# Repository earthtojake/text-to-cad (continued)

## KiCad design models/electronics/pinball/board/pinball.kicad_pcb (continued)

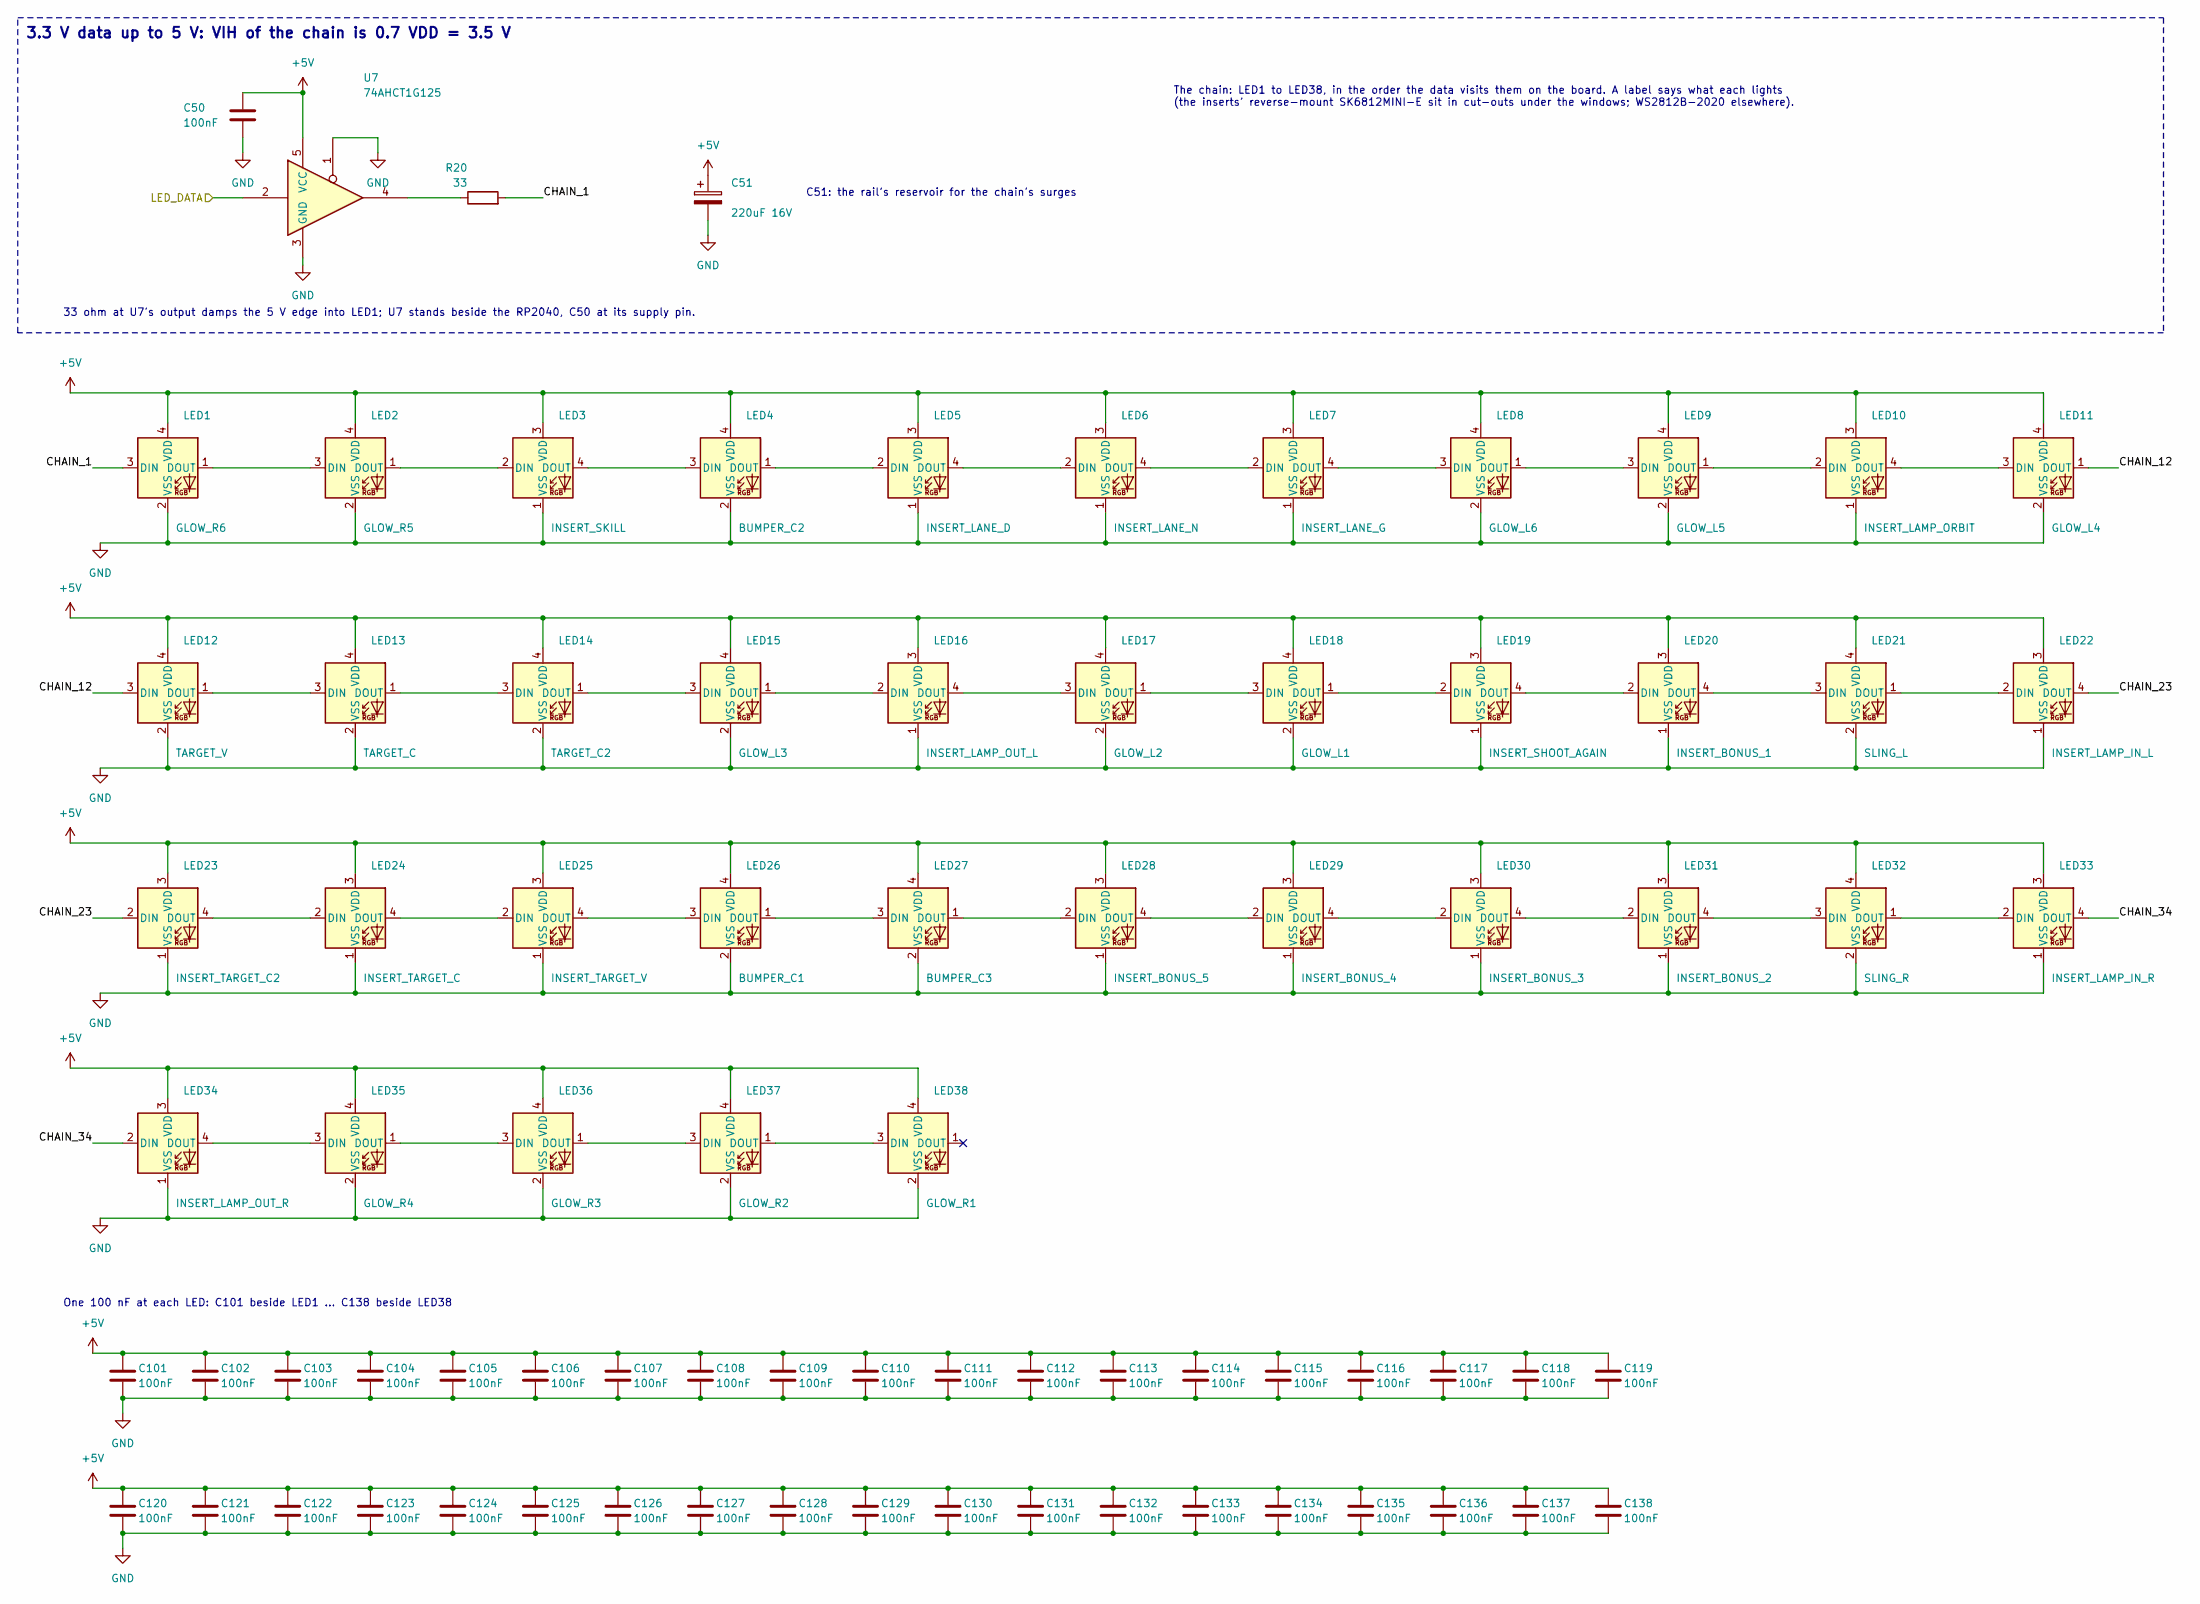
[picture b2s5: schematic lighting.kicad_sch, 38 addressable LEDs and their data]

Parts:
C50, C101, C102, C103, C104, C105, C106, C107, C108, C109, C110, C111, C112, C113, C114, C115, C116, C117, C118, C119, C120, C121, C122, C123, C124, C125, C126, C127, C128, C129, C130, C131, C132, C133, C134, C135, C136, C137, C138: 100nF; C_0402_1005Metric; MPN CL05B104KO5NNNC; LCSC C1525
C51: 220uF 16V; CP_Elec_8x10; MPN EEE-FK1C221P
LED1: GLOW_R6; LED_WS2812B-2020_PLCC4_2.0x2.0mm; MPN WS2812B-2020; LCSC C965555
LED2: GLOW_R5; LED_WS2812B-2020_PLCC4_2.0x2.0mm; MPN WS2812B-2020; LCSC C965555
LED3: INSERT_SKILL; LED_SK6812MINI-E_3.2x2.8mm_P1.5mm_ReverseMount; MPN SK6812MINI-E; LCSC C5149201
LED4: BUMPER_C2; LED_WS2812B-2020_PLCC4_2.0x2.0mm; MPN WS2812B-2020; LCSC C965555
LED5: INSERT_LANE_D; LED_SK6812MINI-E_3.2x2.8mm_P1.5mm_ReverseMount; MPN SK6812MINI-E; LCSC C5149201
LED6: INSERT_LANE_N; LED_SK6812MINI-E_3.2x2.8mm_P1.5mm_ReverseMount; MPN SK6812MINI-E; LCSC C5149201
LED7: INSERT_LANE_G; LED_SK6812MINI-E_3.2x2.8mm_P1.5mm_ReverseMount; MPN SK6812MINI-E; LCSC C5149201
LED8: GLOW_L6; LED_WS2812B-2020_PLCC4_2.0x2.0mm; MPN WS2812B-2020; LCSC C965555
LED9: GLOW_L5; LED_WS2812B-2020_PLCC4_2.0x2.0mm; MPN WS2812B-2020; LCSC C965555
LED10: INSERT_LAMP_ORBIT; LED_SK6812MINI-E_3.2x2.8mm_P1.5mm_ReverseMount; MPN SK6812MINI-E; LCSC C5149201
LED11: GLOW_L4; LED_WS2812B-2020_PLCC4_2.0x2.0mm; MPN WS2812B-2020; LCSC C965555
LED12: TARGET_V; LED_WS2812B-2020_PLCC4_2.0x2.0mm; MPN WS2812B-2020; LCSC C965555
LED13: TARGET_C; LED_WS2812B-2020_PLCC4_2.0x2.0mm; MPN WS2812B-2020; LCSC C965555
LED14: TARGET_C2; LED_WS2812B-2020_PLCC4_2.0x2.0mm; MPN WS2812B-2020; LCSC C965555
LED15: GLOW_L3; LED_WS2812B-2020_PLCC4_2.0x2.0mm; MPN WS2812B-2020; LCSC C965555
LED16: INSERT_LAMP_OUT_L; LED_SK6812MINI-E_3.2x2.8mm_P1.5mm_ReverseMount; MPN SK6812MINI-E; LCSC C5149201
LED17: GLOW_L2; LED_WS2812B-2020_PLCC4_2.0x2.0mm; MPN WS2812B-2020; LCSC C965555
LED18: GLOW_L1; LED_WS2812B-2020_PLCC4_2.0x2.0mm; MPN WS2812B-2020; LCSC C965555
LED19: INSERT_SHOOT_AGAIN; LED_SK6812MINI-E_3.2x2.8mm_P1.5mm_ReverseMount; MPN SK6812MINI-E; LCSC C5149201
LED20: INSERT_BONUS_1; LED_SK6812MINI-E_3.2x2.8mm_P1.5mm_ReverseMount; MPN SK6812MINI-E; LCSC C5149201
LED21: SLING_L; LED_WS2812B-2020_PLCC4_2.0x2.0mm; MPN WS2812B-2020; LCSC C965555
LED22: INSERT_LAMP_IN_L; LED_SK6812MINI-E_3.2x2.8mm_P1.5mm_ReverseMount; MPN SK6812MINI-E; LCSC C5149201
LED23: INSERT_TARGET_C2; LED_SK6812MINI-E_3.2x2.8mm_P1.5mm_ReverseMount; MPN SK6812MINI-E; LCSC C5149201
LED24: INSERT_TARGET_C; LED_SK6812MINI-E_3.2x2.8mm_P1.5mm_ReverseMount; MPN SK6812MINI-E; LCSC C5149201
LED25: INSERT_TARGET_V; LED_SK6812MINI-E_3.2x2.8mm_P1.5mm_ReverseMount; MPN SK6812MINI-E; LCSC C5149201
LED26: BUMPER_C1; LED_WS2812B-2020_PLCC4_2.0x2.0mm; MPN WS2812B-2020; LCSC C965555
LED27: BUMPER_C3; LED_WS2812B-2020_PLCC4_2.0x2.0mm; MPN WS2812B-2020; LCSC C965555
LED28: INSERT_BONUS_5; LED_SK6812MINI-E_3.2x2.8mm_P1.5mm_ReverseMount; MPN SK6812MINI-E; LCSC C5149201
LED29: INSERT_BONUS_4; LED_SK6812MINI-E_3.2x2.8mm_P1.5mm_ReverseMount; MPN SK6812MINI-E; LCSC C5149201
LED30: INSERT_BONUS_3; LED_SK6812MINI-E_3.2x2.8mm_P1.5mm_ReverseMount; MPN SK6812MINI-E; LCSC C5149201
LED31: INSERT_BONUS_2; LED_SK6812MINI-E_3.2x2.8mm_P1.5mm_ReverseMount; MPN SK6812MINI-E; LCSC C5149201
LED32: SLING_R; LED_WS2812B-2020_PLCC4_2.0x2.0mm; MPN WS2812B-2020; LCSC C965555
LED33: INSERT_LAMP_IN_R; LED_SK6812MINI-E_3.2x2.8mm_P1.5mm_ReverseMount; MPN SK6812MINI-E; LCSC C5149201
LED34: INSERT_LAMP_OUT_R; LED_SK6812MINI-E_3.2x2.8mm_P1.5mm_ReverseMount; MPN SK6812MINI-E; LCSC C5149201
LED35: GLOW_R4; LED_WS2812B-2020_PLCC4_2.0x2.0mm; MPN WS2812B-2020; LCSC C965555
LED36: GLOW_R3; LED_WS2812B-2020_PLCC4_2.0x2.0mm; MPN WS2812B-2020; LCSC C965555
LED37: GLOW_R2; LED_WS2812B-2020_PLCC4_2.0x2.0mm; MPN WS2812B-2020; LCSC C965555
LED38: GLOW_R1; LED_WS2812B-2020_PLCC4_2.0x2.0mm; MPN WS2812B-2020; LCSC C965555
R20: 33; R_0402_1005Metric; MPN 0402WGF330JTCE; LCSC C25105
U7: 74AHCT1G125; SOT-23-5; MPN SN74AHCT1G125DBVR; LCSC C7484

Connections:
+5V: C50.1, C51.1, C101.1, C102.1, C103.1, C104.1, C105.1, C106.1, C107.1, C108.1, C109.1, C110.1, C111.1, C112.1, C113.1, C114.1, C115.1, C116.1, C117.1, C118.1, C119.1, C120.1, C121.1, C122.1, C123.1, C124.1, C125.1, C126.1, C127.1, C128.1, C129.1, C130.1, C131.1, C132.1, C133.1, C134.1, C135.1, C136.1, C137.1, C138.1, LED1.4 (VDD), LED2.4 (VDD), LED3.3 (VDD), LED4.4 (VDD), LED5.3 (VDD), LED6.3 (VDD), LED7.3 (VDD), LED8.4 (VDD), LED9.4 (VDD), LED10.3 (VDD), LED11.4 (VDD), LED12.4 (VDD), LED13.4 (VDD), LED14.4 (VDD), LED15.4 (VDD), LED16.3 (VDD), LED17.4 (VDD), LED18.4 (VDD), LED19.3 (VDD), LED20.3 (VDD), LED21.4 (VDD), LED22.3 (VDD), LED23.3 (VDD), LED24.3 (VDD), LED25.3 (VDD), LED26.4 (VDD), LED27.4 (VDD), LED28.3 (VDD), LED29.3 (VDD), LED30.3 (VDD), LED31.3 (VDD), LED32.4 (VDD), LED33.3 (VDD), LED34.3 (VDD), LED35.4 (VDD), LED36.4 (VDD), LED37.4 (VDD), LED38.4 (VDD), U7.5 (VCC); also elsewhere on the board
/Lighting/CHAIN_1: LED1.3 (DIN), R20.2
/Lighting/CHAIN_12: LED11.1 (DOUT), LED12.3 (DIN)
/Lighting/CHAIN_23: LED22.4 (DOUT), LED23.2 (DIN)
/Lighting/CHAIN_34: LED33.4 (DOUT), LED34.2 (DIN)
/Lighting/LED_DATA: U7.2; also elsewhere on the board
GND: C50.2, C51.2, C101.2, C102.2, C103.2, C104.2, C105.2, C106.2, C107.2, C108.2, C109.2, C110.2, C111.2, C112.2, C113.2, C114.2, C115.2, C116.2, C117.2, C118.2, C119.2, C120.2, C121.2, C122.2, C123.2, C124.2, C125.2, C126.2, C127.2, C128.2, C129.2, C130.2, C131.2, C132.2, C133.2, C134.2, C135.2, C136.2, C137.2, C138.2, LED1.2 (VSS), LED2.2 (VSS), LED3.1 (VSS), LED4.2 (VSS), LED5.1 (VSS), LED6.1 (VSS), LED7.1 (VSS), LED8.2 (VSS), LED9.2 (VSS), LED10.1 (VSS), LED11.2 (VSS), LED12.2 (VSS), LED13.2 (VSS), LED14.2 (VSS), LED15.2 (VSS), LED16.1 (VSS), LED17.2 (VSS), LED18.2 (VSS), LED19.1 (VSS), LED20.1 (VSS), LED21.2 (VSS), LED22.1 (VSS), LED23.1 (VSS), LED24.1 (VSS), LED25.1 (VSS), LED26.2 (VSS), LED27.2 (VSS), LED28.1 (VSS), LED29.1 (VSS), LED30.1 (VSS), LED31.1 (VSS), LED32.2 (VSS), LED33.1 (VSS), LED34.1 (VSS), LED35.2 (VSS), LED36.2 (VSS), LED37.2 (VSS), LED38.2 (VSS), U7.1, U7.3 (GND); also elsewhere on the board
unnamed: LED1.1 (DOUT), LED2.3 (DIN)
unnamed: LED2.1 (DOUT), LED3.2 (DIN)
unnamed: LED3.4 (DOUT), LED4.3 (DIN)
unnamed: LED4.1 (DOUT), LED5.2 (DIN)
unnamed: LED5.4 (DOUT), LED6.2 (DIN)
unnamed: LED6.4 (DOUT), LED7.2 (DIN)
unnamed: LED7.4 (DOUT), LED8.3 (DIN)
unnamed: LED8.1 (DOUT), LED9.3 (DIN)
unnamed: LED9.1 (DOUT), LED10.2 (DIN)
unnamed: LED10.4 (DOUT), LED11.3 (DIN)
unnamed: LED12.1 (DOUT), LED13.3 (DIN)
unnamed: LED13.1 (DOUT), LED14.3 (DIN)
unnamed: LED14.1 (DOUT), LED15.3 (DIN)
unnamed: LED15.1 (DOUT), LED16.2 (DIN)
unnamed: LED16.4 (DOUT), LED17.3 (DIN)
unnamed: LED17.1 (DOUT), LED18.3 (DIN)
unnamed: LED18.1 (DOUT), LED19.2 (DIN)
unnamed: LED19.4 (DOUT), LED20.2 (DIN)
unnamed: LED20.4 (DOUT), LED21.3 (DIN)
unnamed: LED21.1 (DOUT), LED22.2 (DIN)
unnamed: LED23.4 (DOUT), LED24.2 (DIN)
unnamed: LED24.4 (DOUT), LED25.2 (DIN)
unnamed: LED25.4 (DOUT), LED26.3 (DIN)
unnamed: LED26.1 (DOUT), LED27.3 (DIN)
unnamed: LED27.1 (DOUT), LED28.2 (DIN)
unnamed: LED28.4 (DOUT), LED29.2 (DIN)
unnamed: LED29.4 (DOUT), LED30.2 (DIN)
unnamed: LED30.4 (DOUT), LED31.2 (DIN)
unnamed: LED31.4 (DOUT), LED32.3 (DIN)
unnamed: LED32.1 (DOUT), LED33.2 (DIN)
unnamed: LED34.4 (DOUT), LED35.3 (DIN)
unnamed: LED35.1 (DOUT), LED36.3 (DIN)
unnamed: LED36.1 (DOUT), LED37.3 (DIN)
unnamed: LED37.1 (DOUT), LED38.3 (DIN)
unnamed: R20.1, U7.4

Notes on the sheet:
3.3 V data up to 5 V: VIH of the chain is 0.7 VDD = 3.5 V
33 ohm at U7's output damps the 5 V edge into LED1; U7 stands beside the RP2040, C50 at its supply pin.
C51: the rail's reservoir for the chain's surges
The chain: LED1 to LED38, in the order the data visits them on the board. A label says what each lights (the inserts' reverse-mount SK6812MINI-E sit in cut-outs under the windows; WS2812B-2020 elsewhere).
One 100 nF at each LED: C101 beside LED1 ... C138 beside LED38

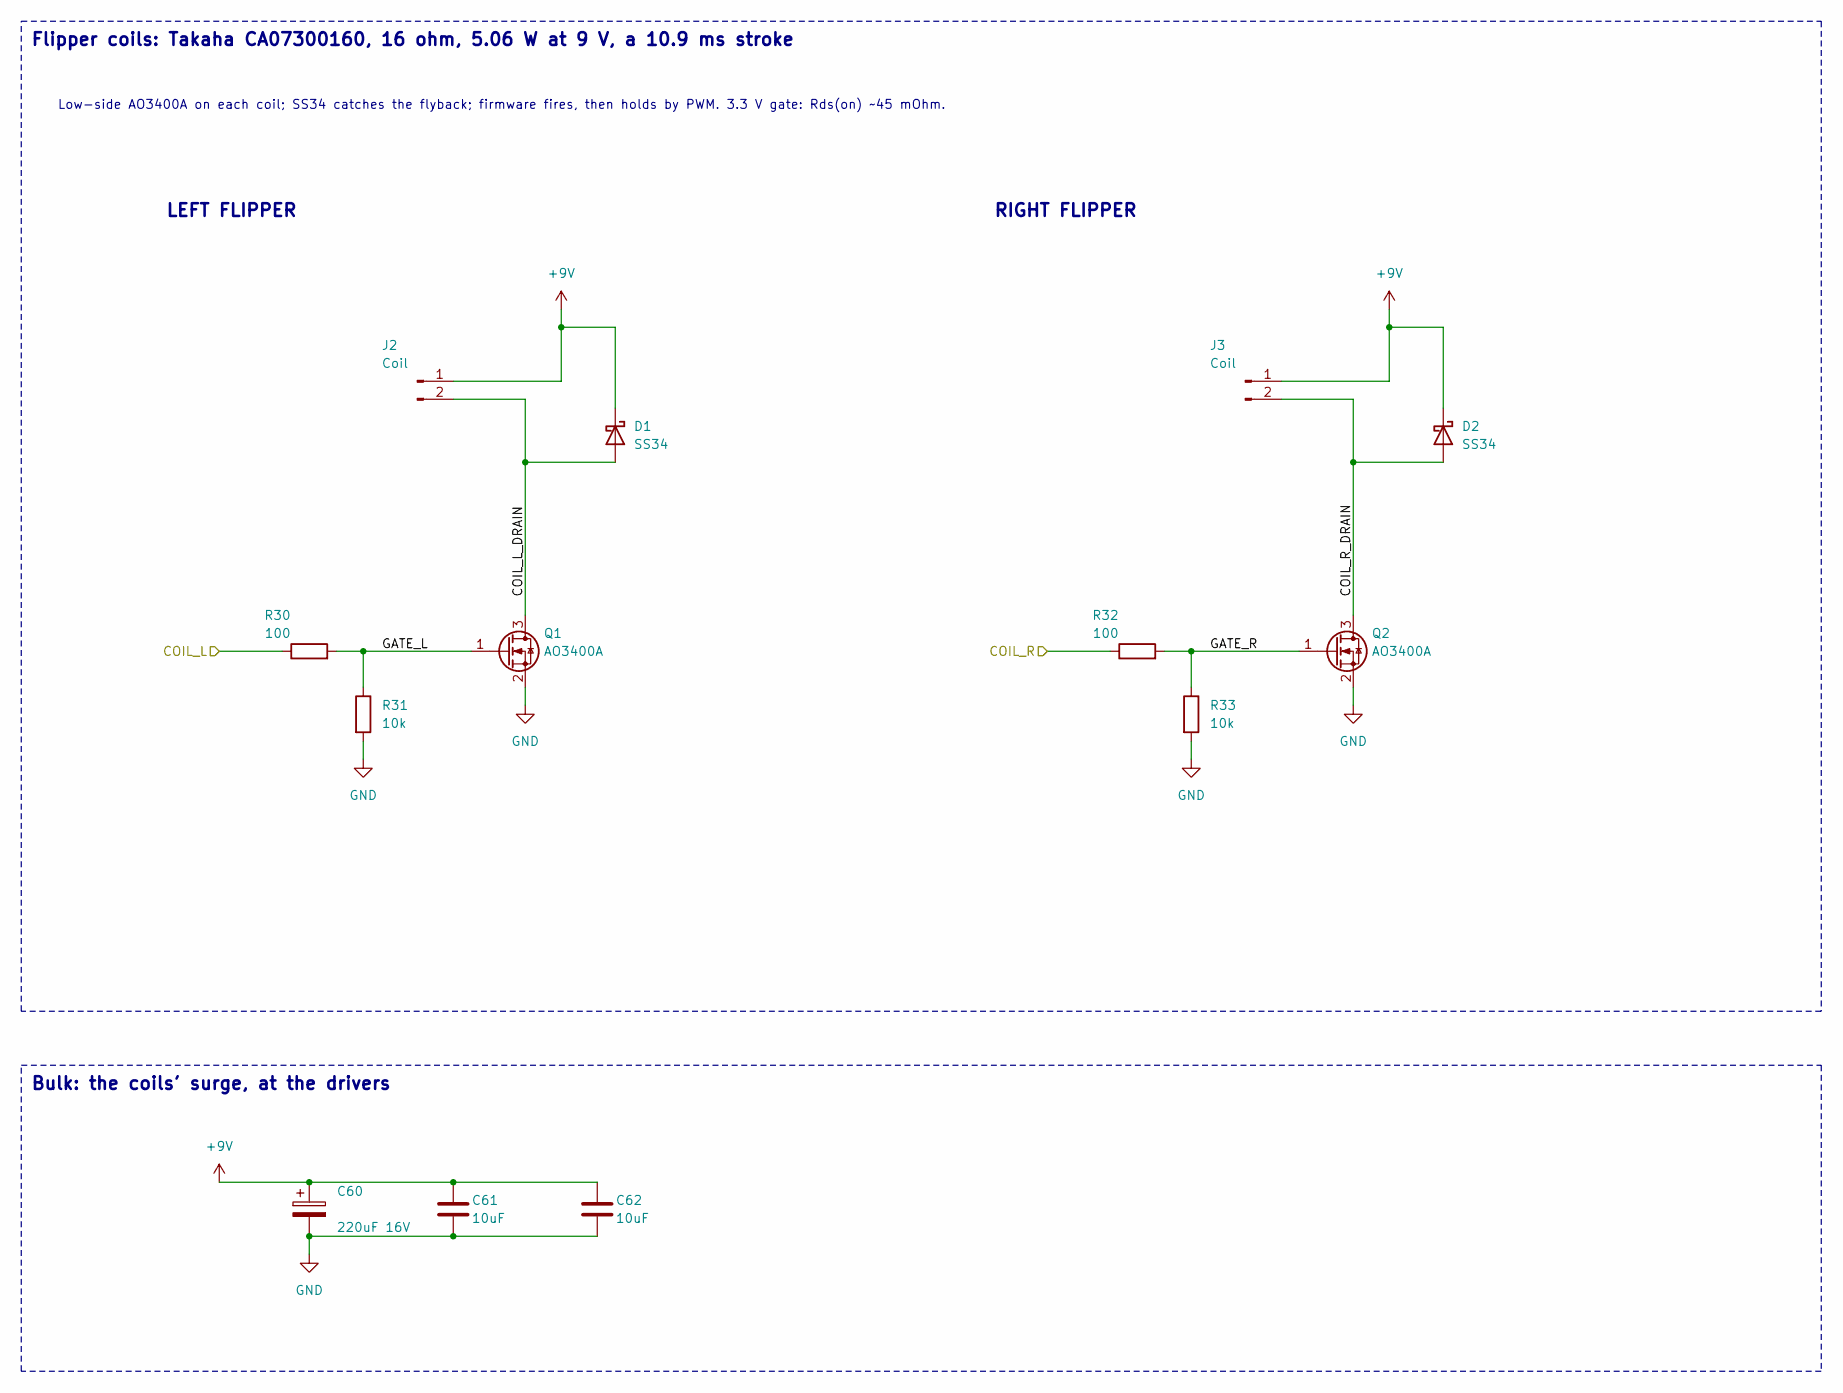
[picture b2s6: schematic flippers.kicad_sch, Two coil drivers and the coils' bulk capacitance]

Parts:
C60: 220uF 16V; CP_Elec_8x10; MPN EEE-FK1C221P
C61, C62: 10uF; C_0805_2012Metric; MPN CL21A106KAYNNNE; LCSC C15850
D1, D2: SS34; D_SMA; MPN SS34; LCSC C8678
J2, J3: Coil; JST_PH_B2B-PH-K_1x02_P2.00mm_Vertical; MPN B2B-PH-K-S; LCSC C131337
Q1, Q2: AO3400A; SOT-23; MPN AO3400A; LCSC C20917
R30, R32: 100; R_0402_1005Metric; MPN 0402WGF1000TCE; LCSC C25076
R31, R33: 10k; R_0402_1005Metric; MPN 0402WGF1002TCE; LCSC C25744

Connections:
+9V: C60.1, C61.1, C62.1, D1.1 (K), D2.1 (K), J2.1, J3.1; also elsewhere on the board
/Flippers/COIL_L: R30.1; also elsewhere on the board
/Flippers/COIL_L_DRAIN: D1.2 (A), J2.2, Q1.3 (D)
/Flippers/COIL_R: R32.1; also elsewhere on the board
/Flippers/COIL_R_DRAIN: D2.2 (A), J3.2, Q2.3 (D)
/Flippers/GATE_L: Q1.1 (G), R30.2, R31.1
/Flippers/GATE_R: Q2.1 (G), R32.2, R33.1
GND: C60.2, C61.2, C62.2, Q1.2 (S), Q2.2 (S), R31.2, R33.2; also elsewhere on the board

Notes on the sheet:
Flipper coils: Takaha CA07300160, 16 ohm, 5.06 W at 9 V, a 10.9 ms stroke
Low-side AO3400A on each coil; SS34 catches the flyback; firmware fires, then holds by PWM. 3.3 V gate: Rds(on) ~45 mOhm.
LEFT FLIPPER
RIGHT FLIPPER
Bulk: the coils' surge, at the drivers

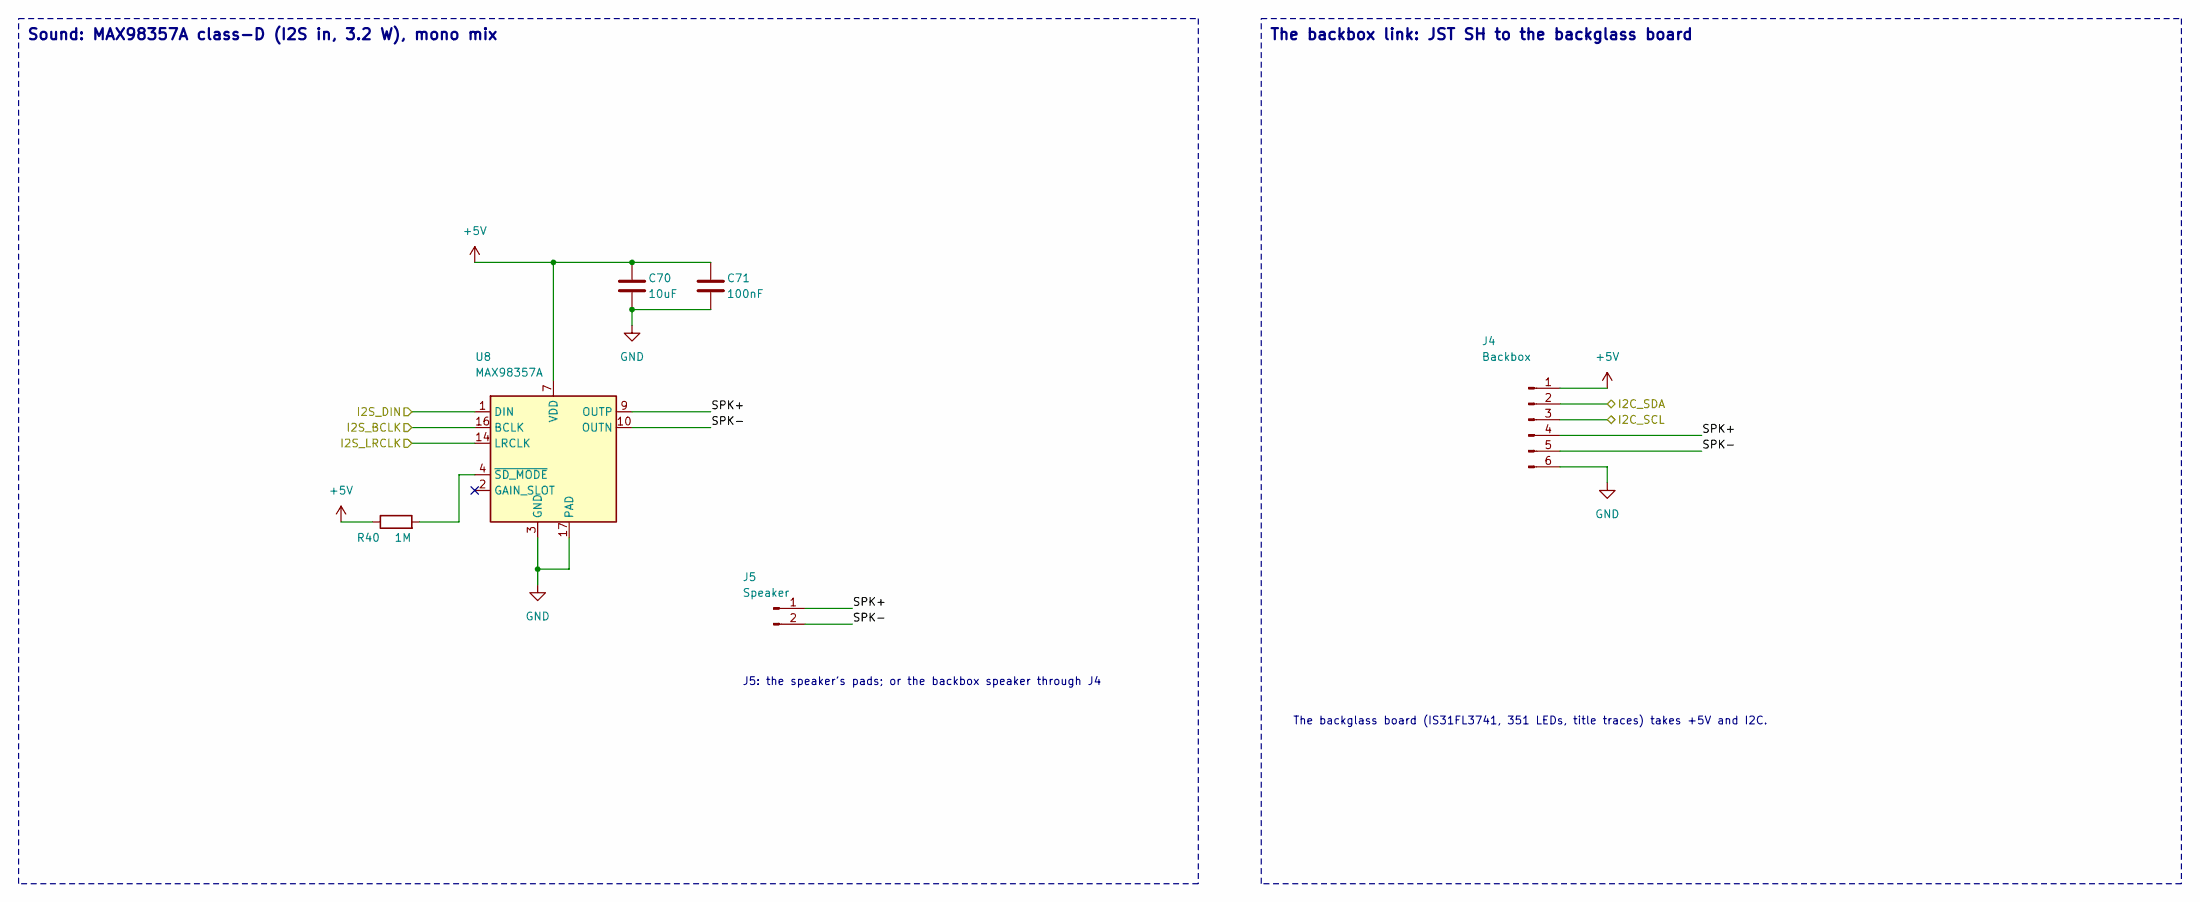
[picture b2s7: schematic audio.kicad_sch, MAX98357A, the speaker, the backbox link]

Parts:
C70: 10uF; C_0805_2012Metric; MPN CL21A106KAYNNNE; LCSC C15850
C71: 100nF; C_0402_1005Metric; MPN CL05B104KO5NNNC; LCSC C1525
J4: Backbox; JST_SH_SM06B-SRSS-TB_1x06-1MP_P1.00mm_Horizontal; MPN SM06B-SRSS-TB; LCSC C160404
J5: Speaker; SpeakerPads_2x3mm
R40: 1M; R_0402_1005Metric; MPN 0402WGF1004TCE; LCSC C26083
U8: MAX98357A; TQFN-16-1EP_3x3mm_P0.5mm_EP1.23x1.23mm; MPN MAX98357AETE+T; LCSC C910544

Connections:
+5V: C70.1, C71.1, J4.1, R40.1, U8.7 (VDD), U8.8 (VDD); also elsewhere on the board
/Audio and backbox/I2S_BCLK: U8.16 (BCLK); also elsewhere on the board
/Audio and backbox/I2S_DIN: U8.1 (DIN); also elsewhere on the board
/Audio and backbox/I2S_LRCLK: U8.14 (LRCLK); also elsewhere on the board
/Audio and backbox/SPK+: J4.4, J5.1, U8.9 (OUTP)
/Audio and backbox/SPK-: J4.5, J5.2, U8.10 (OUTN)
/I2C_SCL: J4.3; also elsewhere on the board
/I2C_SDA: J4.2; also elsewhere on the board
GND: C70.2, C71.2, J4.6, U8.3 (GND), U8.11 (GND), U8.15 (GND), U8.17 (PAD); also elsewhere on the board
unnamed: R40.2, U8.4 (~SD_MODE)

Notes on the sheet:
Sound: MAX98357A class-D (I2S in, 3.2 W), mono mix
J5: the speaker's pads; or the backbox speaker through J4
The backbox link: JST SH to the backglass board
The backglass board (IS31FL3741, 351 LEDs, title traces) takes +5V and I2C.

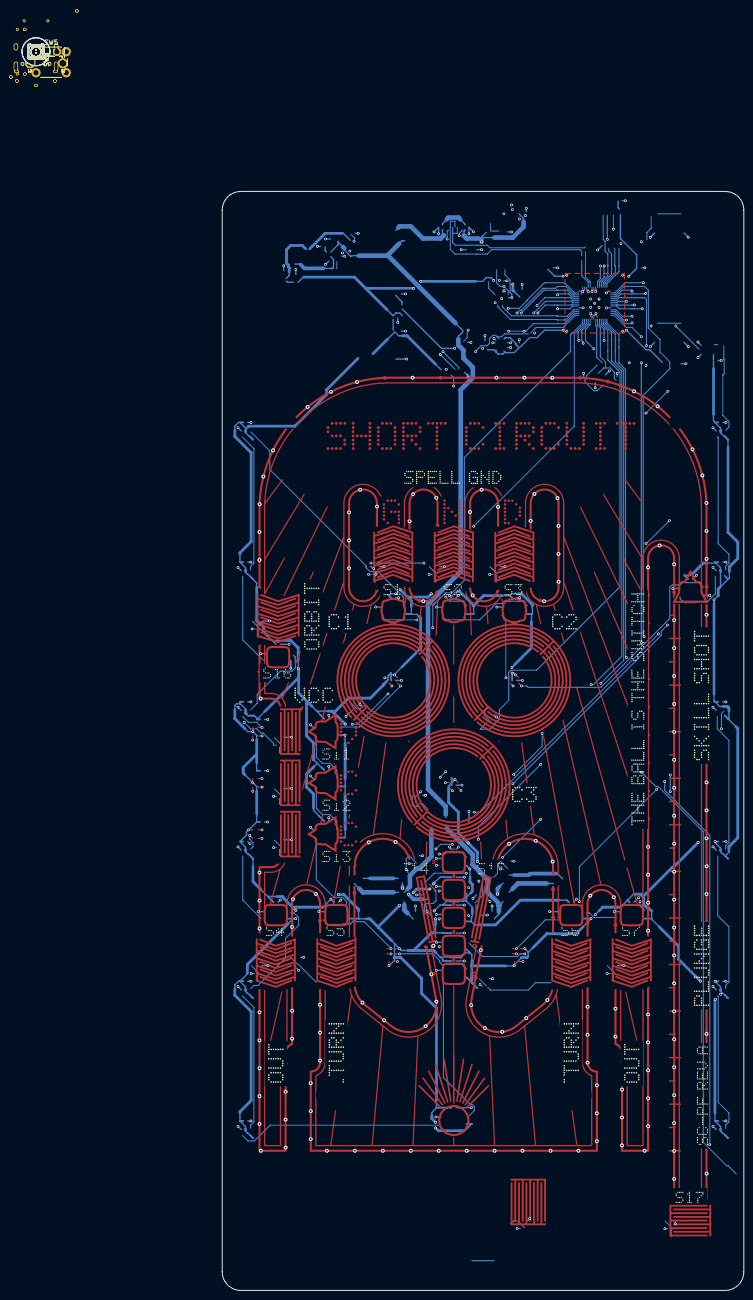
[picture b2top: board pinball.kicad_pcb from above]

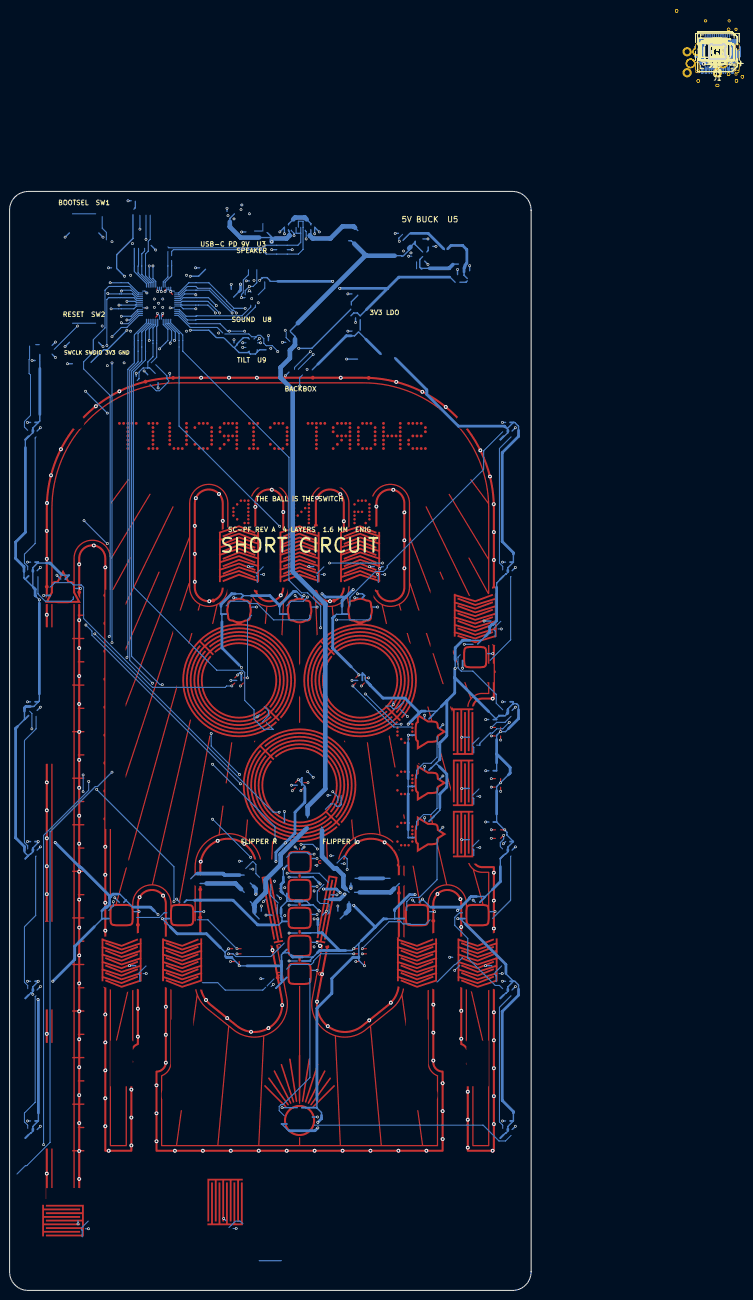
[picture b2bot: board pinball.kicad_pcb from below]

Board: 4 copper layers, 3.6 x 3.2 mm, 250 parts (173 on the bottom side), 125 nets.

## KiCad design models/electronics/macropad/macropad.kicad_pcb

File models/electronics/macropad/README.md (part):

# Nine: a 3x3 RP2040 macropad, board and case designed together

**Build the board first.** Its KiCad files (the board, the four schematic sheets, the project file and its rules,
the footprint library) are generated by `scripts/`, not committed: `cad run build.py`, from this folder, makes them
in about 20 s. It needs the `cad` command (KiCad 10.99's kicad-cli and API come with it) and KiCad's stock libraries
(macOS's KiCad.app, or `KICAD10_SYMBOL_DIR` and `KICAD10_FOOTPRINT_DIR`). Opening the board or the schematic in the
viewer or in KiCad, the checks and the case (`src/`) all read what it writes, so run it before any of them.

Nine is a nine-key mechanical macropad with a knob: an RP2040 with 16 MB of QSPI flash, USB-C, nine
hot-swap MX switches each with its own RGB LED shining through the switch, and an EC11 rotary
encoder with a push switch. Its 3D-printed case (a tray and an integrated switch plate) is generated
from the board file: the switch cut-outs, the screw bosses, the encoder window, the USB-C opening
and the BOOT/RESET pinholes are all read from `macropad.kicad_pcb`, so moving a part on the board
and running the case again moves the case's feature with it.

Why it is interesting to watch: a familiar, desirable object goes from a schematic to a routed,
DRC-clean two-layer board to a printable case and an exploding assembly, every step a prompt.

## The parts

| Ref | Part | Why |
| --- | --- | --- |
| U1 | RP2040 (QFN-56) | dual Cortex-M0+, native USB 1.1 full speed, 30 GPIO |
| U2 | W25Q128JVSIQ, 16 MB QSPI flash (SOIC-8) | the RP2040 boots from it |
| Y1 | 12 MHz crystal, ABM8-272-T3 (3225), 15 pF loads, 1 k on XOUT | RP2040's reference design values |
| U3 | AP2112K-3.3 LDO, 600 mA | 3.3 V from USB 5 V |
| J1 | GCT USB4105-GF-A, USB-C 2.0 receptacle | with 5.1 k Rd on CC1/CC2 (R1, R2): a USB-C sink |
| U4 | Nexperia PRTR5V0U2X | ESD clamps on D+/D- (shunt type, so the pair runs straight past it) |
| F1 | 500 mA polyfuse | VBUS to +5V |
| SW1-SW9 | Kailh CPG151101S11 MX hot-swap sockets | 19.05 mm pitch, plate-mount MX switches |
| D1-D9 | SK6812MINI-E reverse-mount RGB | under each switch's LED window, chained |
| U5 | 74AHCT1G125 | 3.3 V -> 5 V data for the LEDs (VIH 0.7 VDD = 3.5 V) |
| SW10 | Alps EC11E with switch, 20 mm shaft | the knob |
| SW11, SW12 | Omron B3U-1000P | BOOTSEL and RESET, pressed through the tray |
| TP1-TP4 | test pads | SWCLK, SWDIO, GND, 3V3 |
| H1-H6 | M2 holes | four between the keys, two in the back corners |

**Direct wiring, no matrix.** Nine keys, three encoder lines and the LED data use 13 of the RP2040's
30 GPIOs, so each key has its own pin (internal pull-up, switch to ground): no diodes (nine fewer
parts), every combination of keys reads without ghosting, and the firmware is a plain GPIO read. A
3x3 matrix would save 3 pins the board does not need.

**Every SMD part is on the bottom.** The hot-swap sockets and the reverse-mount LEDs have to be there
anyway, so the whole board assembles in one SMT pass; the top holds only the switches (in their
sockets) and the encoder. Two copper layers: the bottom carries the parts, the signals and power, the
top is a ground pour crossed only by the key lines in channels between the key columns (under the
switches' plastic) and a few short hops.

## The board

| | |
| --- | --- |
| Size | 59.0 x 83.5 mm, 1.6 mm FR-4, rounded corners r 3 mm |
| Layers | 2 (1 oz); both are ground pours |
| Parts | 73 footprints: 63 to assemble (all SMD on the bottom; the encoder is through-hole), 6 M2 holes, 4 test pads |
| Nets | 46 connected (KiCad adds 21 more, one on each unconnected pin) |
| Routing | 371 tracks, 1384 mm of copper, 81 vias; 0 unconnected |
| ERC | clean, 0 warnings (`cad kicad_sch erc macropad.kicad_sch`) |
| DRC | clean: 0 errors, 0 warnings (`cad kicad_pcb drc macropad.kicad_pcb` on the built board) |
| Rules | JLCPCB standard 2-layer, read 2026-11-04 from the pcb skill's table of jlcpcb.com/capabilities: 0.15 mm space (fab 0.10), 0.2 mm signal tracks, 0.3/0.6 mm vias, 0.3 mm copper to edge (0.2 at the LEDs' own cut-outs, the fab's limit) |

Hierarchical schematic: the root (`macropad.kicad_sch`) and three sheets, `usb_power` (USB-C, CC,
ESD, polyfuse, LDO), `mcu` (RP2040, flash, crystal, boot, reset, SWD, decoupling) and `keys`
(switches, encoder, level shifter, LEDs, holes). GPIO map: ENC_SW GP0, ENC_B GP1, ENC_A GP2,
KEY9/6/3 GP3/4/5, KEY8/5/2 GP9/10/11, KEY7/4/1 GP26/27/29, LED data GP28. The map was chosen from
the board: each group leaves the RP2040 on the side facing where it goes, in the order it arrives.

The RP2040's own ring (between its pads and its exposed pad) carries two rails, 1V1 from VREG_VOUT
to both DVDD pins and 3V3 to IOVDD 1, 10 and 22, which keeps the USB pair and the QSPI fan-out
uncrossed on a two-layer board.

KiCad's library has no MX hot-swap footprint and no 3D model for a keyboard switch or an EC11, so the
project carries its own: `macropad.pretty` holds the hot-swap socket's footprint (drawn from the Kailh
CPG151101S11 land pattern, mirrored for the bottom) and KiCad's EC11 footprint naming a model, and
`src/vendor_parts.py` draws both models. Check the socket's land pattern against a real socket before
ordering.

Review (guided, not a fab's CAM check): DRC clean against the rules above; every pad on its
schematic pin's net, all track segments at 45-degree steps, no track narrower than its current
(+5V/VBUS 0.5 mm for 0.6 A), each decoupler within 3 mm of its pin and ground under every point of
the USB pair (`check_macropad.py`); USB pair skew 0.6 mm (connector side) and 1.1 mm (MCU side),
immaterial at full speed's 83 ns bits. Items for a person: C13 (USB_VDD + IOVDD 49) sits 4.5 mm from
its pins (the spot beside them holds the USB pair and the QSPI fan-out); DVDD 50 has no cap of its own
(it is ringed to VREG_VOUT 45's 1 uF and DVDD 23's 100 nF); IOVDD 22's cap C9 is placed by pin 33;
the LED supply (0.54 A at full white) exceeds USB 2.0's 500 mA: firmware must cap brightness. The
stock SK6812MINI-E footprint's pads sit 0.247 mm from its own cut-out, so a custom rule allows 0.2 mm
(JLCPCB's limit) for the LEDs; its pin numbers differ from the OPSCO datasheet's, but symbol and
footprint agree and each pad sits where the mirrored top view puts its function. Not checked: Gerbers
in a Gerber viewer, impedance, the BOM's sourcing beyond the LCSC numbers given, the hot-swap land
pattern against a physical socket.

## The case

Printed in PLA or PETG on an FDM printer, all parts without supports:

- **Tray** (floor down): 2 mm floor 5.4 mm under the board, 2.4 mm walls 0.4 mm off the board's
  edge, six bosses (6 mm) with M2 x 3 mm heat-set insert holes (3.2 mm) under the board's holes, a
  13 mm USB-C slot at the receptacle, 2.5 mm pinholes under BOOT and RESET.
- **Plate** (top face down): 1.5 mm, its top 5.0 mm above the board (MX), a 14.1 mm cut-out at each
  key, the encoder body's window, 4.6 mm spacer bosses down to the board at each hole (M2 clearance
  2.4 mm), NINE stencilled beside the knob.
- **Keycaps** (top down, x9): one shape, legend-free, 18 mm base, 12.6 mm top, 7.6 mm tall, MX cross
  4.2 x 1.35 mm; `keycap_body(dish=...)` scoops the top (flat by default, so it prints face down).
- **Knob** (top down): 19 mm, 24 grip flutes, a D-bore for the EC11's 6 mm shaft, a pointer groove.

Hardware: six M2 x 10 mm button-head screws (through the plate, its spacer and the board into the
tray's inserts), six M2 x 3 mm heat-set inserts, four stick-on rubber feet, nine MX-style switches.

Everything the case is built around comes from `macropad.kicad_pcb` through
`src/lib/board_geometry.py`: the outline and its corner radius, the six holes, the nine switch
positions, the encoder's shaft and body (and its rotation, which turns the knob's D-bore), the USB
receptacle's x and mating face, the two buttons.

## Files

| Path | What |
| --- | --- |
| `build.py` | the one command that makes the KiCad project: every step of `scripts/` in order |
| `scripts/` | the source of the board: footprints, schematic, rules, netlist import, placement, routing, silkscreen |
| `fp-lib-table`, `sym-lib-table` | the project's library tables (KiCad's stock libraries through `${KICAD10_FOOTPRINT_DIR}` and `${KICAD10_SYMBOL_DIR}`), the only KiCad files kept: no script writes them |
| `check_macropad.py` | the board's own checks |
| `src/` | the case: `vendor_parts.py` (the socket, the EC11 and an MX switch), `case.py`, `assembly.py`, `check_fit.py`, `exports.py`, `lib/board_geometry.py` |

Nothing generated is committed: the KiCad project `build.py` writes (`macropad.kicad_pro`, `.kicad_pcb`,
`.kicad_dru`, `macropad.kicad_sch` and its `usb_power`, `mcu` and `keys` sheets, `macropad.pretty/`, all in KiCad
10.99's format), the footprints' 3D models (`macropad.3dshapes/`), the fabrication files (`fab/`), the board's STEP
and the case's files (`STEP/`, `XBF/`, `GLB/`, `3MF/`, `DXF/`) are written by the commands below, and `.gitignore`
keeps them out of Git.

## Rebuild

From this folder, with the `cad` command. KiCad's stock libraries are named through
`${KICAD10_SYMBOL_DIR}` and `${KICAD10_FOOTPRINT_DIR}`, which ERC and DRC read in the KiCad you installed:
nothing to set. The generators (`gen_footprints.py`, `gen_schematic.py`) read the same libraries in macOS's
KiCad.app; elsewhere, give them KiCad's folders in those two variables.

```bash
# the board and its schematic, from scripts/ (each step states the board it wants; rerunning is harmless)
cad run build.py                           # about 20 s: the steps below, in order
#   scripts/gen_footprints.py              macropad.pretty
#   scripts/gen_schematic.py               the four sheets
#   scripts/step1_import.py                the board (KiCad makes it, with its project) and the netlist
#   scripts/step0_rules.py                 JLCPCB rules and netclasses into the project, the custom rules
#   scripts/step2_place.py                 outline, every part's place, side and angle
#   scripts/route.py                       every track and via, then the pours
#   scripts/step4_silk.py                  silkscreen

# the 3D models KiCad's library lacks: run this before opening the board in 3D or exporting its STEP or GLB
cad run src/vendor_parts.py                # macropad.3dshapes/: the hot-swap socket and the EC11

# check the board
cad kicad_sch erc macropad.kicad_sch
cad kicad_pcb drc macropad.kicad_pcb
cad run check_macropad.py                  # prints nothing when the board is clean

# fabrication files
for k in gerbers drill pos bom pdf; do cad kicad_pcb export macropad.kicad_pcb --to $k -o fab/$k; done
cad kicad_sch export macropad.kicad_sch --to pdf -o fab/schematic
cad kicad_pcb export macropad.kicad_pcb --to dxf -o DXF     # the outline and drilled holes
cad kicad_pcb export macropad.kicad_pcb --to glb -o GLB     # the board with its parts, to look at

# the case, read from the board: its STEP with every part, converted once to an xbf
cad kicad_pcb export macropad.kicad_pcb --to step -o STEP   # STEP/macropad.step
cad step export STEP/macropad.step XBF/macropad.xbf
cad run src/case.py                        # tray, plate, keycap, knob and their print orientations
cad run src/assembly.py                    # nine (with its explode) and nine_exploded
cad run src/check_fit.py                   # overlap volumes and clearances against the board's STEP
cad run src/exports.py                     # 3MF/ and STEP/ of each printed part, STEP/nine.step, GLB/nine.glb
cad threemf dfm 3MF/tray.3mf --process printing --angle-limit 45 --samples 20000   # and plate, keycap, knob
```

`gen_footprints.py`, `gen_schematic.py` and `step0_rules.py` write the same files on every run; the layout steps
make the same board, its items under new ids.

## The case's checks

**Fit** (`src/check_fit.py`, against KiCad's STEP of the board with every part): 297 pairs of solids
whose boxes meet, overlap volume 0 for all (tray, plate, switches, keycaps and knob each against
every board solid; switches, keycaps and knob against the plate; tray against plate). The board
rests on the tray's bosses (distance 0) with 0.4 mm to the tray's walls; the tray's floor is
2.0 mm under the lowest bottom part (the USB-C receptacle, z -3.4); the plate's underside is
3.59 mm above the bare board (MX: 3.5 plus the copper); each keycap is 1.2 mm clear of its switch;
the knob's D-bore sits on the EC11's shaft with the bore turned to the encoder's rotation.

**Printing** (`cad threemf dfm 3MF/<part>.3mf --process printing --angle-limit 45 --samples 20000`; FDM limits
from the cad skill's printing reference: 1.2 mm supported wall, 45 degrees, 10 mm bridge):

| Part | Overhangs under 45 deg | Walls min / p05 | Support | Result |
| --- | --- | --- | --- | --- |
| tray (floor down) | 0 mm2 | 1.38 / 2.0 mm | 0 | pass |
| plate (top down) | 0 mm2 | 0.04 / 1.5 mm | 0 | review: the thin readings are the acute inside corner of the stencil N, a wedge down to its tip; the plate is 1.5 mm |
| keycap (top down) | 0 mm2 | 0.53 / 1.2 mm | 0 | review: the MX cross (4.2 x 1.35 mm) inside the 5.5 mm stem leaves 0.53 mm at the cross's ends; the stem cannot grow (it travels into the switch's 5.6 mm opening). Print with a 0.25 mm nozzle, or in resin |
| knob (top down) | 3 mm2 (the 1 mm pointer groove, on the bed face) | 0.25 / 5.08 mm | 3 mm3 | review: the pointer groove ends 0.25 mm from the flute beyond it, for the groove's 1 mm depth |

What the check found and what changed: the tray's foot recesses (220 mm2 of 0.8 mm ceilings and
1.0 mm floors) are gone (stick-on feet instead) and the screw pilots stop 1.4 mm above the bed; the
plate's corner spacers at H5/H6 thinned to 0.55 mm against the tray's corner and are gone (the wall
carries the plate there); the engraved NINE (43 mm2 of ceilings face down) is now a through stencil;
the knob's flutes run full height (no ceilings), and its pointer groove, first modelled 0.1 mm under
the top face (a sealed void under a 0.1 mm skin), is open on the top. Not measured by the check:
minimum hole (the paperclip holes are 2.5 mm, the screw holes 2.4 mm, both over FDM's 2.0), bridges
(none), fit of the heat-set inserts (3.2 mm holes for M2 x 3 inserts, the insert maker's figure).

## Demo video script (about 3 minutes)

Record the CAD app (or the viewer) beside the agent's chat. Every prompt is what the person types;
the agent runs the skills. Pre-build everything once the day before so each shot replays warm.

| # | Prompt (typed to the agent) | What the viewer shows | Length | The one thing |
| --- | --- | --- | --- | --- |
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
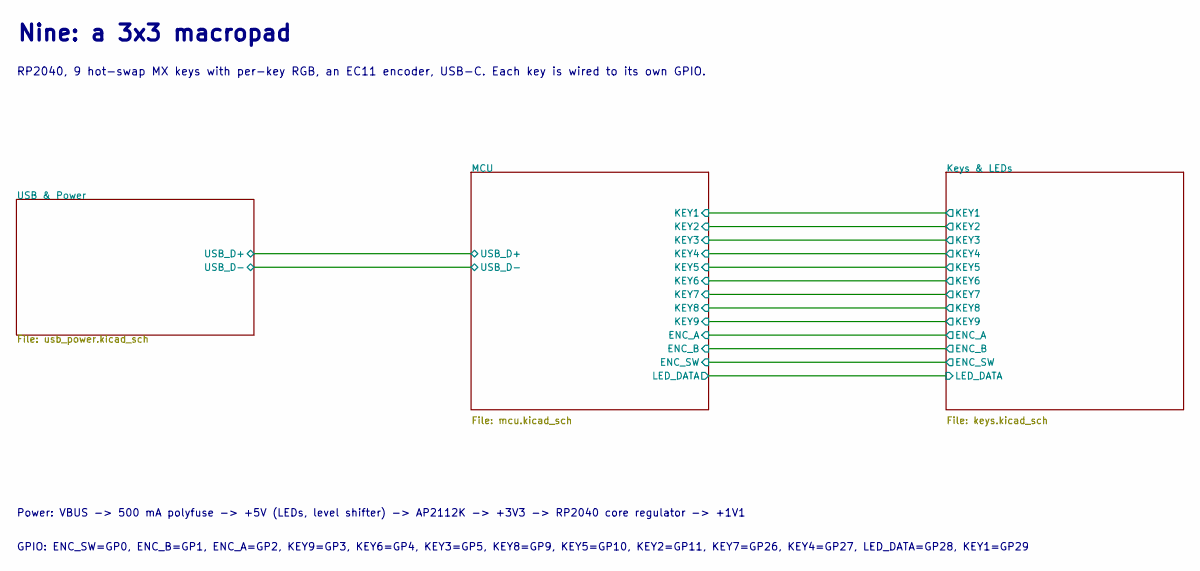
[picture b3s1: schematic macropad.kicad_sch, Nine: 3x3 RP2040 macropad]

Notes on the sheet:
Nine: a 3x3 macropad
RP2040, 9 hot-swap MX keys with per-key RGB, an EC11 encoder, USB-C. Each key is wired to its own GPIO.
Power: VBUS -> 500 mA polyfuse -> +5V (LEDs, level shifter) -> AP2112K -> +3V3 -> RP2040 core regulator -> +1V1
GPIO: ENC_SW=GP0, ENC_B=GP1, ENC_A=GP2, KEY9=GP3, KEY6=GP4, KEY3=GP5, KEY8=GP9, KEY5=GP10, KEY2=GP11, KEY7=GP26, KEY4=GP27, LED_DATA=GP28, KEY1=GP29

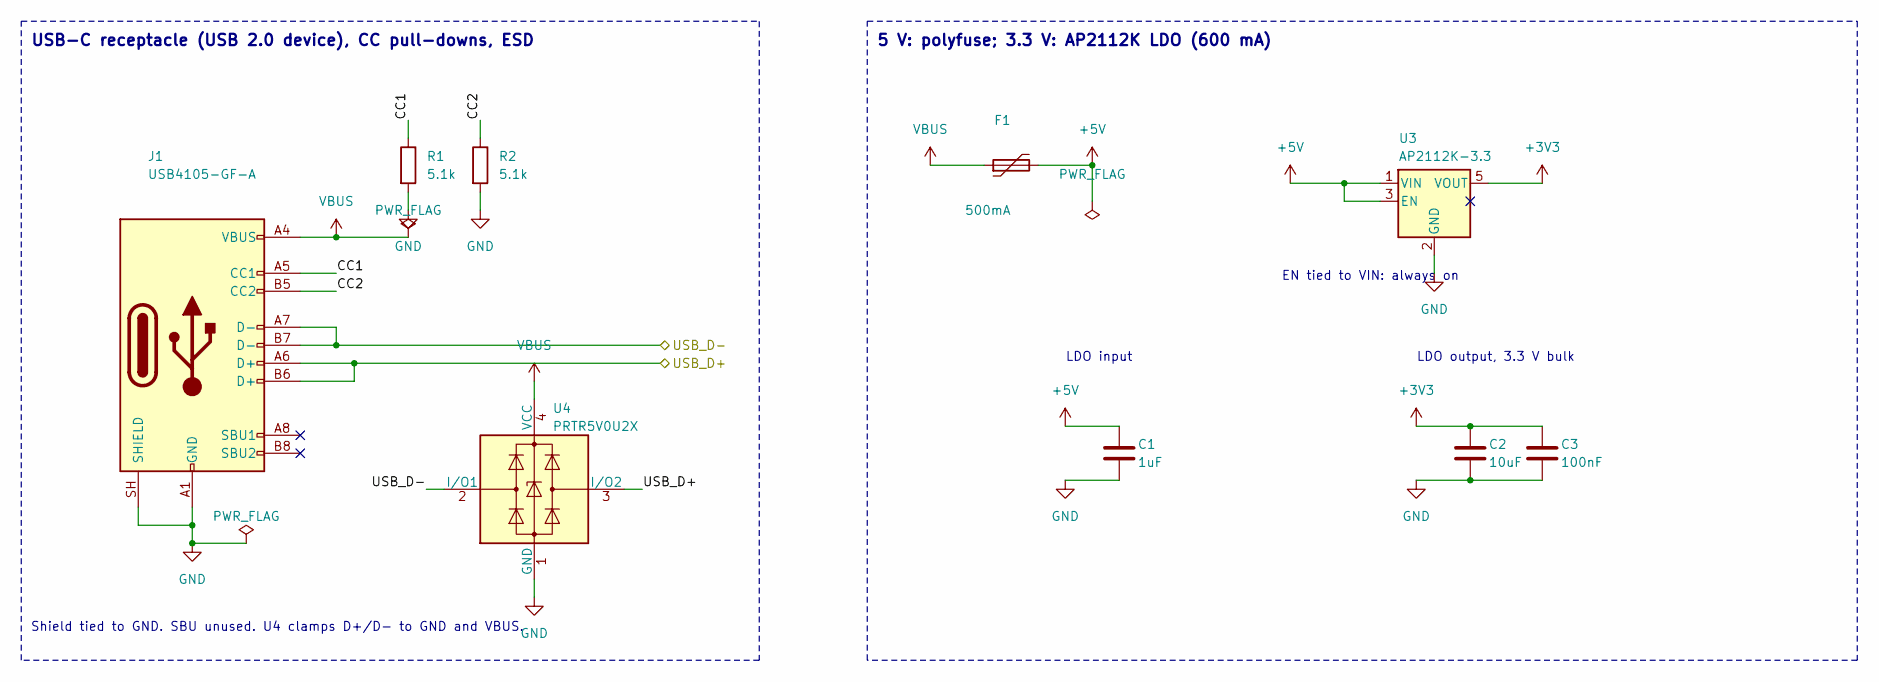
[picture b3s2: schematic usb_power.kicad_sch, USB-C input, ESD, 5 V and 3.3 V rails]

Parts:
C1: 1uF; C_0402_1005Metric; MPN CL05A105KA5NQNC; LCSC C52923
C2: 10uF; C_0805_2012Metric; MPN CL21A106KAYNNNE; LCSC C15850
C3: 100nF; C_0402_1005Metric; MPN CL05B104KO5NNNC; LCSC C1525
F1: 500mA; Fuse_1206_3216Metric; MPN 0ZCJ0050FF2E
J1: USB4105-GF-A; USB_C_Receptacle_GCT_USB4105-xx-A_16P_TopMnt_Horizontal; MPN USB4105-GF-A
R1, R2: 5.1k; R_0402_1005Metric; MPN 0402WGF5101TCE; LCSC C25905
U3: AP2112K-3.3; SOT-23-5; MPN AP2112K-3.3TRG1; LCSC C51118
U4: PRTR5V0U2X; SOT-143; MPN PRTR5V0U2X,215; LCSC C12333

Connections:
+3V3: C2.1, C3.1, U3.5 (VOUT); also elsewhere on the board
+5V: C1.1, F1.2, U3.1 (VIN), U3.3 (EN); also elsewhere on the board
/USB & Power/CC1: J1.A5 (CC1), R1.1
/USB & Power/CC2: J1.B5 (CC2), R2.1
/USB & Power/USB_D+: J1.A6 (D+), J1.B6 (D+), U4.3 (I/O2); also elsewhere on the board
/USB & Power/USB_D-: J1.A7 (D-), J1.B7 (D-), U4.2 (I/O1); also elsewhere on the board
GND: C1.2, C2.2, C3.2, J1.A1 (GND), J1.A12 (GND), J1.B1 (GND), J1.B12 (GND), J1.SH (SHIELD), R1.2, R2.2, U3.2 (GND), U4.1 (GND); also elsewhere on the board
VBUS: F1.1, J1.A4 (VBUS), J1.A9 (VBUS), J1.B4 (VBUS), J1.B9 (VBUS), U4.4 (VCC)

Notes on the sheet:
USB-C receptacle (USB 2.0 device), CC pull-downs, ESD
Shield tied to GND. SBU unused. U4 clamps D+/D- to GND and VBUS.
5 V: polyfuse; 3.3 V: AP2112K LDO (600 mA)
EN tied to VIN: always on
LDO input
LDO output, 3.3 V bulk
